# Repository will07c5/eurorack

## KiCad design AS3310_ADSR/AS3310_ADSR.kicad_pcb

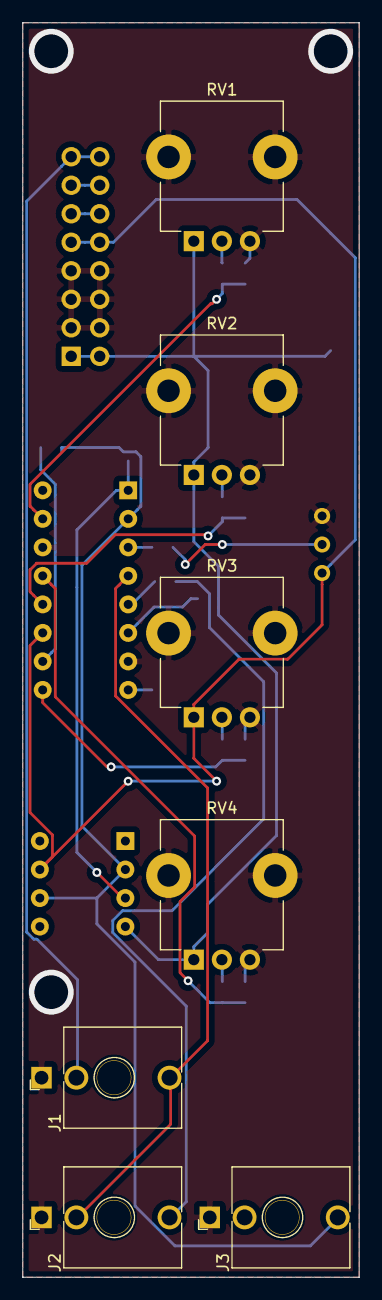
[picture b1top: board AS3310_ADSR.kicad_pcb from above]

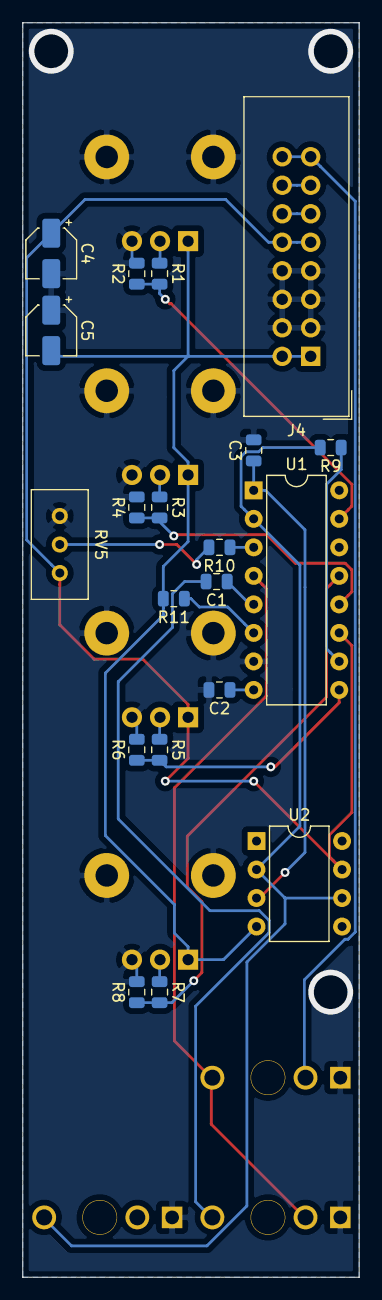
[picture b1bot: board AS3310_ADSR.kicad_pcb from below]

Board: 2 copper layers, 30.0 x 111.8 mm, 27 parts (20 on the bottom side), 24 nets.

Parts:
C1: 3nF; C_0805_2012Metric
C2: 10nF; C_0805_2012Metric
C3: 39nF; C_0805_2012Metric
C4, C5: CP1; CP_Elec_4x3
J1: Gate; Jack_3.5mm_QingPu_WQP-PJ398SM_Vertical_CircularHoles
J2: Trigger; Jack_3.5mm_QingPu_WQP-PJ398SM_Vertical_CircularHoles
J3: Env; Jack_3.5mm_QingPu_WQP-PJ398SM_Vertical_CircularHoles
J4: Conn_01x16; IDC-Header_2x08_P2.54mm_Vertical
R1, R3, R7: 22K; R_0805_2012Metric
R2, R4, R8: 450; R_0805_2012Metric
R5, R6: R_US; R_0805_2012Metric
R9: 30K; R_0805_2012Metric
R10: 10K; R_0805_2012Metric
R11: 470; R_0805_2012Metric
RV1, RV2, RV3: 100K; Potentiometer_TT_P0915N
RV4: R_POT_US; Potentiometer_TT_P0915N
RV5: 100K; Potentiometer_Bourns_3296W_Vertical
U1: AS3310; DIP-16_W7.62mm
U2: TL071; DIP-8_W7.62mm

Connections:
+5V: J4.11, J4.12
+12V: C4.1, J4.9, J4.10, RV3.1, RV5.1, U1.11, U2.7
-12V: C5.2, J4.1, J4.2, R11.2, RV1.1, RV2.1, RV4.1, U2.4
/Attack: R1.2, R2.1, U1.15
/Decay: R3.2, R4.1, U1.12
/Gate: J1.T, J2.TN, U1.4
/Rear_CV: J4.13, J4.14
/Rear_Gate: J1.TN, J4.15, J4.16
/Release: R7.2, R8.1, U1.13
/Sustain: R5.2, R6.1, U1.9
/Trigger: C1.2, J2.T
GNDREF: C2.2, C3.2, C4.2, C5.1, J1.S, J2.S, J3.S, J4.3, J4.4, J4.5, J4.6, J4.7, J4.8, R2.2, R4.2, R6.2, R8.2, RV1.3, RV2.3, RV3.3, RV4.3, RV5.3, U1.7, U1.14
unnamed: C1.1, U1.5
unnamed: C2.1, U1.8
unnamed: C3.1, U1.1, U2.3
unnamed: J3.T, R9.2, U1.2, U2.2, U2.6
unnamed: R1.1, RV1.2
unnamed: R3.1, RV2.2
unnamed: R5.1, RV3.2
unnamed: R7.1, RV4.2
unnamed: R9.1, U1.10
unnamed: R10.1, U1.3
unnamed: R10.2, RV5.2
unnamed: R11.1, U1.6

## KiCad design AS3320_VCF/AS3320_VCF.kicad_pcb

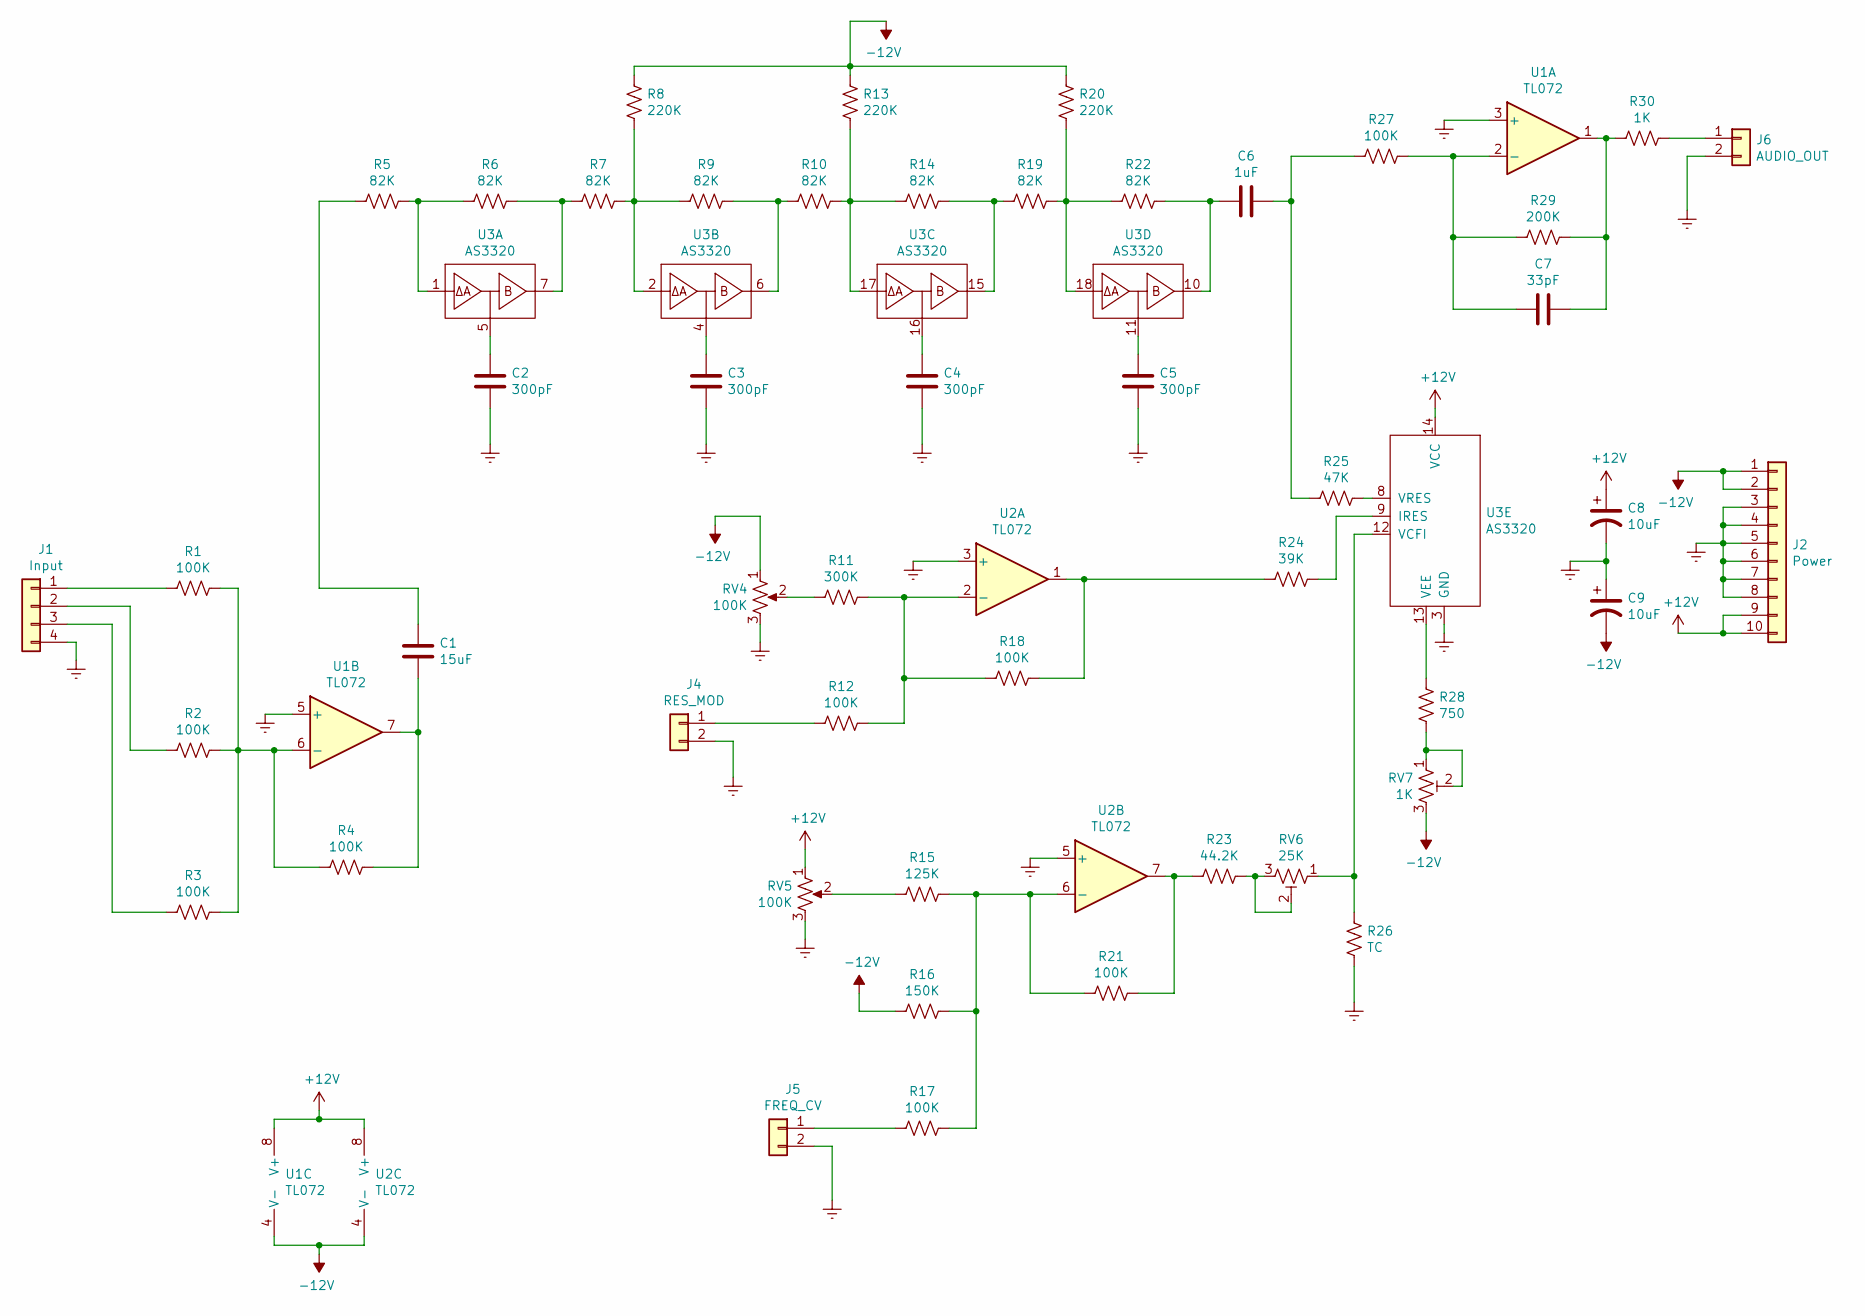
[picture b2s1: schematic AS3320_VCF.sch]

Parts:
C1: 15uF; C_0805_2012Metric
C2, C3, C4, C5: 300pF; Mica_Cap
C6: 1uF; C_0805_2012Metric
C7: 33pF; C_0805_2012Metric
C8, C9: 10uF; CP_Elec_4x3
J1: Input; PinHeader_1x04_P2.54mm_Vertical
J2: Power; IDC-Header_2x05_P2.54mm_Vertical
J4: RES_MOD; PinHeader_1x02_P2.54mm_Vertical
J5: FREQ_CV; PinHeader_1x02_P2.54mm_Vertical
J6: AUDIO_OUT; PinHeader_1x02_P2.54mm_Vertical
R1, R2, R3, R4, R12, R17, R18, R21, R27: 100K; R_0805_2012Metric
R5, R6, R7, R9, R10, R14, R19, R22: 82K; R_0805_2012Metric
R8, R13, R20: 220K; R_0805_2012Metric
R11: 300K; R_0805_2012Metric
R15: 125K; R_0805_2012Metric
R16: 150K; R_0805_2012Metric
R23: 44.2K; R_0805_2012Metric
R24: 39K; R_0805_2012Metric
R25: 47K; R_0805_2012Metric
R26: TC; Tempco
R28: 750; R_0805_2012Metric
R29: 200K; R_0805_2012Metric
R30: 1K; R_0805_2012Metric
RV4, RV5: 100K; PinHeader_1x03_P2.54mm_Vertical
RV6: 25K; Potentiometer_Bourns_3296W_Vertical
RV7: 1K; Potentiometer_Bourns_3296W_Vertical
U1, U2: TL072; DIP-8_W7.62mm
U3: AS3320; DIP-18_W7.62mm

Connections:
+12V: C8.1, J2.9, J2.10, RV5.1, U1.8 (V+), U2.8 (V+), U3.14 (VCC)
-12V: C9.2, J2.1, J2.2, R8.1, R13.1, R16.2, R20.1, RV4.1, RV7.3, U1.4 (V-), U2.4 (V-)
GNDREF: C2.2, C3.2, C4.2, C5.2, C8.2, C9.1, J1.4, J2.3, J2.4, J2.5, J2.6, J2.7, J2.8, J4.2, J5.2, J6.2, R26.2, RV4.3, RV5.3, U1.3 (+), U1.5 (+), U2.3 (+), U2.5 (+), U3.3 (GND)
unnamed: C1.1, R5.2
unnamed: C1.2, R4.1, U1.7
unnamed: C2.1, U3.5
unnamed: C3.1, U3.4
unnamed: C4.1, U3.16
unnamed: C5.1, U3.11
unnamed: C6.1, R25.2, R27.2
unnamed: C6.2, R22.1, U3.10
unnamed: C7.1, R27.1, R29.2, U1.2 (-)
unnamed: C7.2, R29.1, R30.2, U1.1
unnamed: J1.1, R1.2
unnamed: J1.2, R2.2
unnamed: J1.3, R3.2
unnamed: J4.1, R12.2
unnamed: J5.1, R17.2
unnamed: J6.1, R30.1
unnamed: R1.1, R2.1, R3.1, R4.2, U1.6 (-)
unnamed: R5.1, R6.2, U3.1
unnamed: R6.1, R7.2, U3.7
unnamed: R7.1, R8.2, R9.2, U3.2
unnamed: R10.1, R13.2, R14.2, U3.17
unnamed: R9.1, R10.2, U3.6
unnamed: R11.1, R12.1, R18.2, U2.2 (-)
unnamed: R11.2, RV4.2
unnamed: R14.1, R19.2, U3.15
unnamed: R15.1, R16.1, R17.1, R21.2, U2.6 (-)
unnamed: R15.2, RV5.2
unnamed: R18.1, R24.2, U2.1
unnamed: R19.1, R20.2, R22.2, U3.18
unnamed: R21.1, R23.2, U2.7
unnamed: R23.1, RV6.2, RV6.3
unnamed: R24.1, U3.9 (IRES)
unnamed: R25.1, U3.8 (VRES)
unnamed: R26.1, RV6.1, U3.12 (VCFI)
unnamed: R28.1, U3.13 (VEE)
unnamed: R28.2, RV7.1, RV7.2

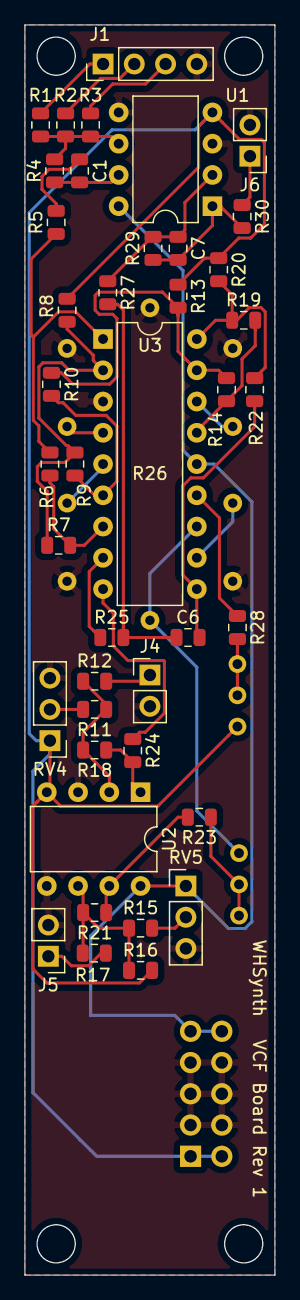
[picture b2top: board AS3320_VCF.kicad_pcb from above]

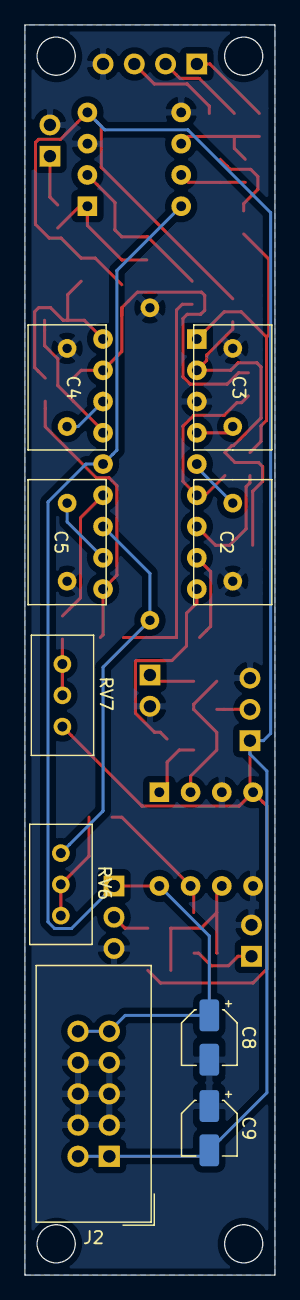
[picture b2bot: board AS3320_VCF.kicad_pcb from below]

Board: 2 copper layers, 20.3 x 101.6 mm, 51 parts (9 on the bottom side), 39 nets.

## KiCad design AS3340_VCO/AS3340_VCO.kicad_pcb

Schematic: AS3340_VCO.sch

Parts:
C1: 1nF; Mica_cap
C2: 100nF; C_0805_2012Metric
C3, C4: 10nF; C_0805_2012Metric
C5, C6: 1nF; C_0805_2012Metric
C7: 560pF; C_0805_2012Metric
C8, C9: 10uF; CP_Elec_4x3
J1: Conn_01x14; PinHeader_1x14_P2.54mm_Vertical
J3: Power; IDC-Header_2x08_P2.54mm_Vertical
JP5: Jumper; PinHeader_1x02_P2.54mm_Vertical
R1: 100K; R_0805_2012Metric
R2, R11: 470; R_0805_2012Metric
R3: 22K; R_0805_2012Metric
R4: 18K; R_0805_2012Metric
R5, R13: 5.6K; R_0805_2012Metric
R6: 1K; R_0805_2012Metric
R7: 680; R_0805_2012Metric
R8: 51K; R_0805_2012Metric
R9: 1M; R_0805_2012Metric
R10: 1.2M; R_0805_2012Metric
RV1: 5K; Potentiometer_Bourns_3296W_Vertical
RV2: 10K; Potentiometer_Bourns_3296W_Vertical
RV3: 1K; Potentiometer_Bourns_3296W_Vertical
RV4: 100K; Potentiometer_Bourns_3296W_Vertical
TP1, TP2: TestPoint; TestPoint_Pad_D2.0mm
U1: AS3340; DIP-16_W7.62mm

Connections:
+5V: J3.11, J3.12
+12V: C8.1, J1.2, J3.9, J3.10, RV2.1, RV4.1, U1.16 (VCC); also elsewhere on the board
-12V: C9.2, J1.3, J3.1, J3.2, R7.2; also elsewhere on the board
/CV: J1.5, R1.1, R2.2, U1.15 (VFCI)
/LIN: C2.2, J1.6
/Output Conditioning/RAW_PULSE: R8.2, U1.4 (VP); also elsewhere on the board
/Output Conditioning/RAW_RAMP: U1.8 (VSO); also elsewhere on the board
/Output Conditioning/RAW_TRI: U1.10 (VTO); also elsewhere on the board
/PWM: J1.4, U1.5 (VPWM)
/Pulse: J1.9; also elsewhere on the board
/REAR_CV: J1.8, J3.13, J3.14
/REAR_GATE: J3.15, J3.16
/Ramp: J1.10; also elsewhere on the board
/SYNC: C5.2, J1.7
/Saw: J1.11; also elsewhere on the board
/Sine: J1.13; also elsewhere on the board
/Tri: J1.12; also elsewhere on the board
/Vee: R5.1, R7.1, R13.1, U1.3 (VEE)
GNDREF: C1.1, C3.1, C4.1, C6.2, C7.1, C8.2, C9.1, J1.1, J1.14, J3.3, J3.4, J3.5, J3.6, J3.7, J3.8, JP5.2, R3.1, R8.1, RV3.2, RV3.3, U1.12 (GND); also elsewhere on the board
unnamed: C1.2, U1.11 (CAP)
unnamed: C2.1, R9.2
unnamed: C3.2, R2.1
unnamed: C4.2, R11.1
unnamed: C5.1, U1.6 (VHSI)
unnamed: C6.1, U1.9 (VSSI)
unnamed: C7.2, JP5.1, R6.2, U1.14 (VS)
unnamed: R1.2, RV4.2, RV4.3
unnamed: R3.2, RV2.3
unnamed: R4.1, RV1.1
unnamed: R4.2, U1.1 (SCALE1)
unnamed: R5.2, TP1.1, U1.2 (SCALE2)
unnamed: R6.1, RV3.1
unnamed: R9.1, R10.1, R11.2, U1.13 (VLFI)
unnamed: R10.2, RV2.2
unnamed: R13.2, RV1.2, RV1.3, TP2.1

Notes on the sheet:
Scale Trim

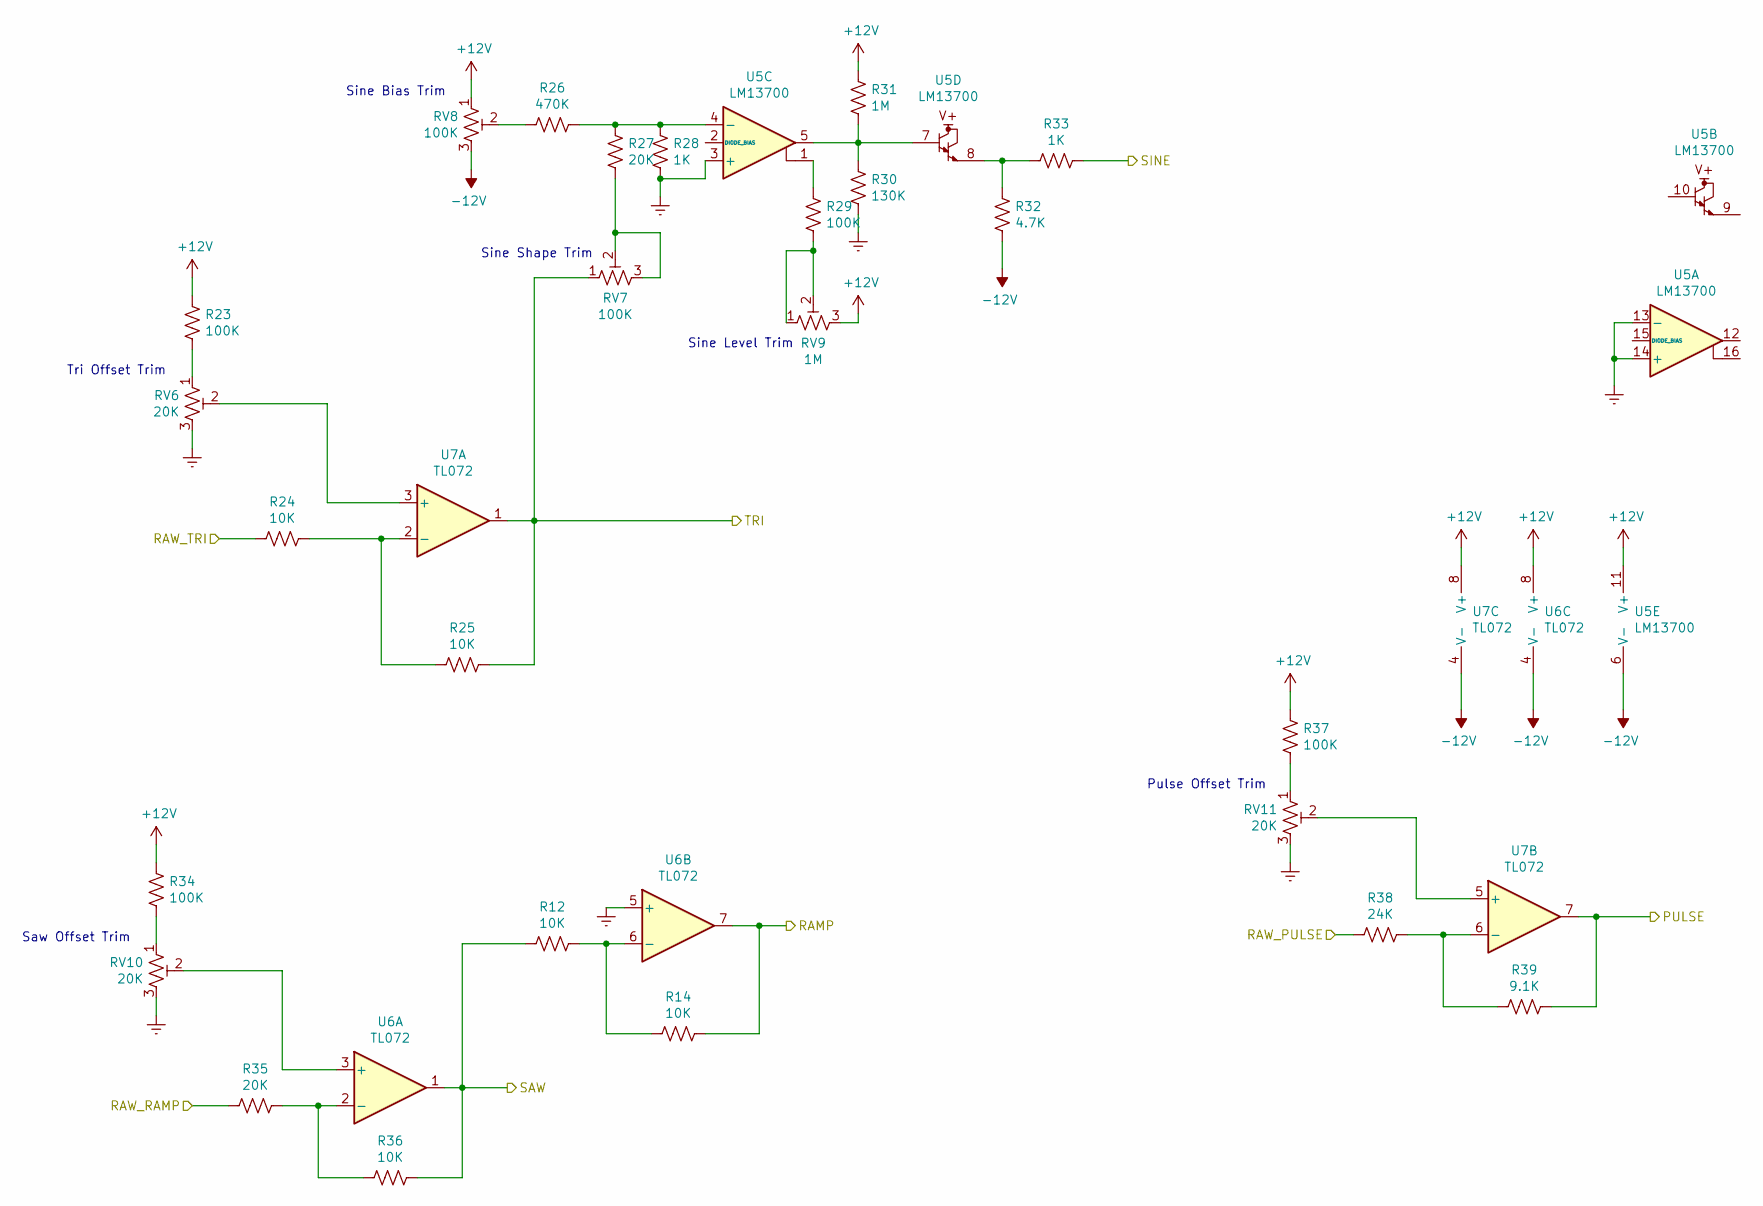
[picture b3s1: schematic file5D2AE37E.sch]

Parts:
R12, R14, R24, R25, R36: 10K; R_0805_2012Metric
R23, R29, R34, R37: 100K; R_0805_2012Metric
R26: 470K; R_0805_2012Metric
R27, R35: 20K; R_0805_2012Metric
R28, R33: 1K; R_0805_2012Metric
R30: 130K; R_0805_2012Metric
R31: 1M; R_0805_2012Metric
R32: 4.7K; R_0805_2012Metric
R38: 24K; R_0805_2012Metric
R39: 9.1K; R_0805_2012Metric
RV6, RV10, RV11: 20K; Potentiometer_Bourns_3296W_Vertical
RV7, RV8: 100K; Potentiometer_Bourns_3296W_Vertical
RV9: 1M; Potentiometer_Bourns_3296W_Vertical
U5: LM13700; DIP-16_W7.62mm
U6, U7: TL072; DIP-8_W7.62mm

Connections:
+12V: R23.1, R31.1, R34.1, R37.1, RV8.1, RV9.3, U5.11 (V+), U6.8 (V+), U7.8 (V+); also elsewhere on the board
-12V: R32.2, RV8.3, U5.6 (V-), U6.4 (V-), U7.4 (V-); also elsewhere on the board
/Output Conditioning/RAW_PULSE: R38.1; also elsewhere on the board
/Output Conditioning/RAW_RAMP: R35.1; also elsewhere on the board
/Output Conditioning/RAW_TRI: R24.1; also elsewhere on the board
/Pulse: R39.2, U7.7; also elsewhere on the board
/Ramp: R14.2, U6.7; also elsewhere on the board
/Saw: R12.1, R36.2, U6.1; also elsewhere on the board
/Sine: R33.2; also elsewhere on the board
/Tri: R25.2, RV7.1, U7.1; also elsewhere on the board
GNDREF: R28.2, R30.2, RV6.3, RV10.3, RV11.3, U5.3 (+), U5.13 (-), U5.14 (+), U6.5 (+); also elsewhere on the board
unnamed: R12.2, R14.1, U6.6 (-)
unnamed: R23.2, RV6.1
unnamed: R24.2, R25.1, U7.2 (-)
unnamed: R26.1, RV8.2
unnamed: R26.2, R27.1, R28.1, U5.4 (-)
unnamed: R27.2, RV7.2, RV7.3
unnamed: R29.1, U5.1
unnamed: R29.2, RV9.1, RV9.2
unnamed: R30.1, R31.2, U5.5, U5.7
unnamed: R32.1, R33.1, U5.8
unnamed: R34.2, RV10.1
unnamed: R35.2, R36.1, U6.2 (-)
unnamed: R37.2, RV11.1
unnamed: R38.2, R39.1, U7.6 (-)
unnamed: RV6.2, U7.3 (+)
unnamed: RV10.2, U6.3 (+)
unnamed: RV11.2, U7.5 (+)

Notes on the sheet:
Tri Offset Trim
Sine Bias Trim
Sine Shape Trim
Sine Level Trim
Saw Offset Trim
Pulse Offset Trim

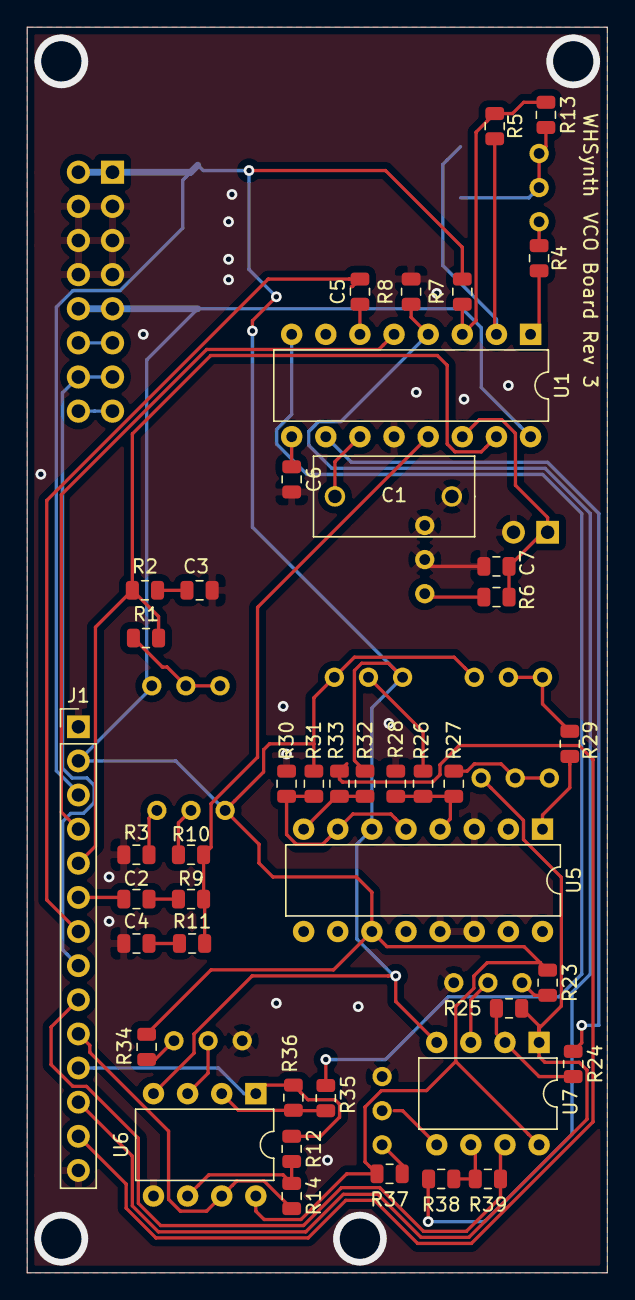
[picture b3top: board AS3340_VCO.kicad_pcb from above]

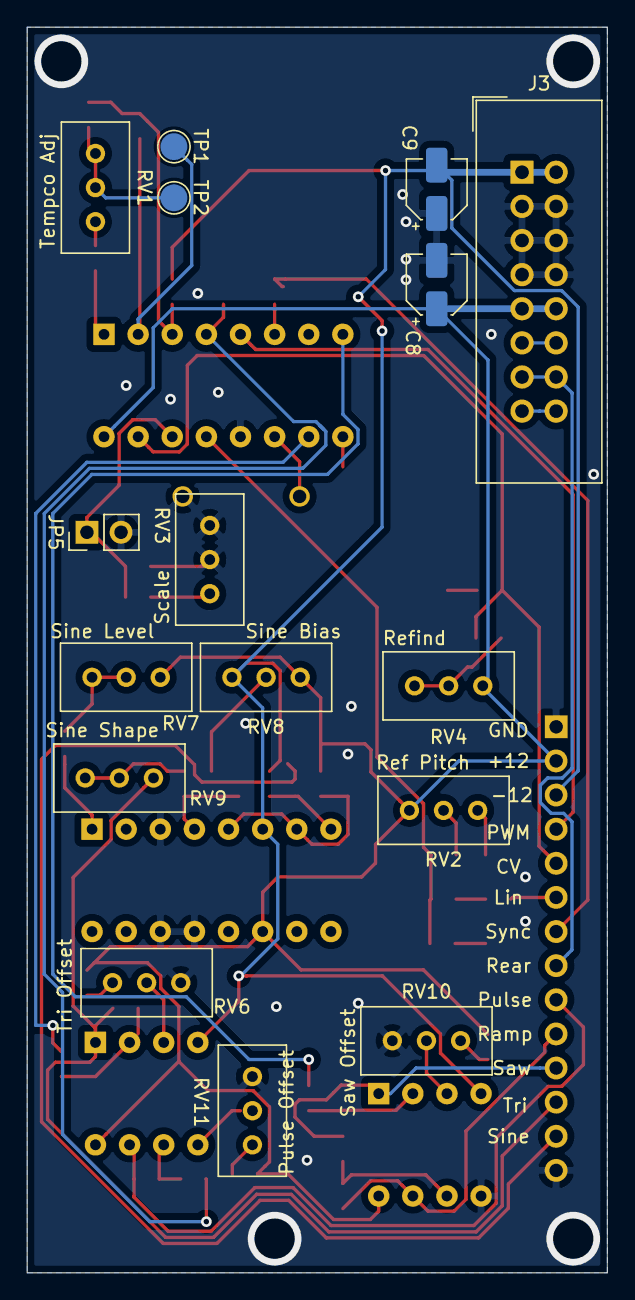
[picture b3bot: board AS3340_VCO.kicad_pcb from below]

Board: 2 copper layers, 43.2 x 92.7 mm, 59 parts (16 on the bottom side), 52 nets.

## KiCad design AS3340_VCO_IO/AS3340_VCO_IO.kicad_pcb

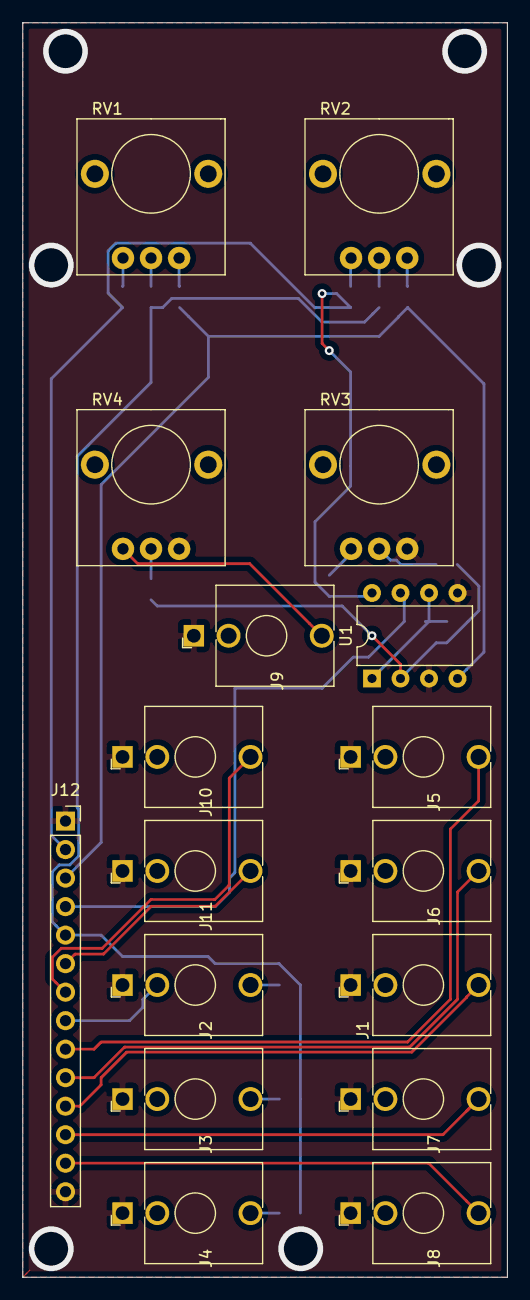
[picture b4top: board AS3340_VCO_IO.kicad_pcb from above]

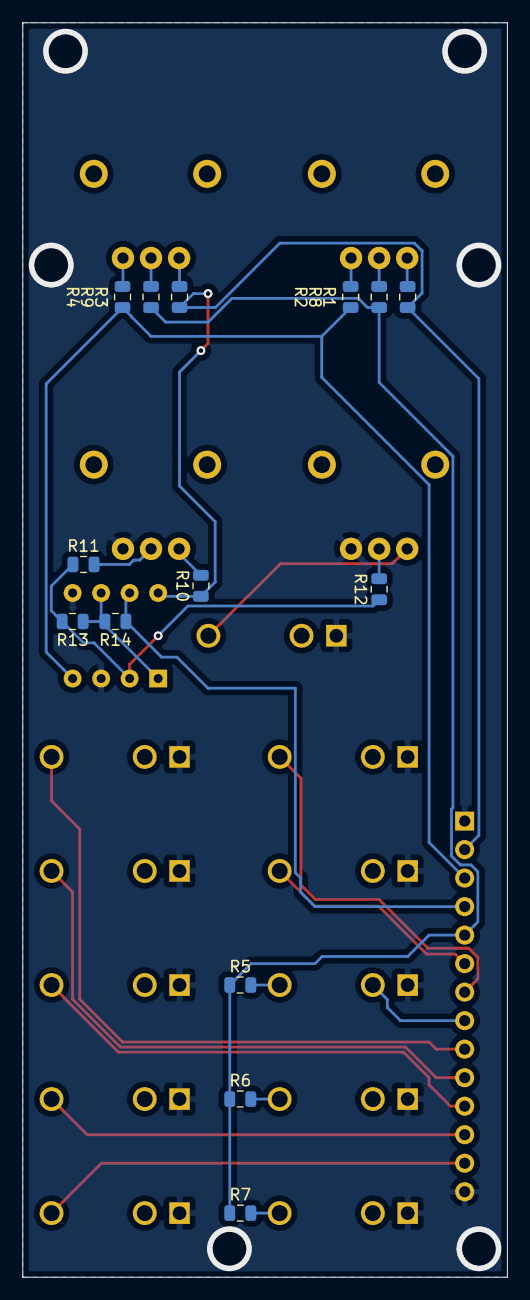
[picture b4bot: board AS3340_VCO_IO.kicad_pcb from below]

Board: 2 copper layers, 43.2 x 111.8 mm, 31 parts (14 on the bottom side), 28 nets.

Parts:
J1: Saw; Jack_3.5mm_QingPu_WQP-PJ398SM_Vertical_CircularHoles
J2: CV1; Jack_3.5mm_QingPu_WQP-PJ398SM_Vertical_CircularHoles
J3: CV2; Jack_3.5mm_QingPu_WQP-PJ398SM_Vertical_CircularHoles
J4: CV3; Jack_3.5mm_QingPu_WQP-PJ398SM_Vertical_CircularHoles
J5: Pulse; Jack_3.5mm_QingPu_WQP-PJ398SM_Vertical_CircularHoles
J6: Ramp; Jack_3.5mm_QingPu_WQP-PJ398SM_Vertical_CircularHoles
J7: Tri; Jack_3.5mm_QingPu_WQP-PJ398SM_Vertical_CircularHoles
J8: Sine; Jack_3.5mm_QingPu_WQP-PJ398SM_Vertical_CircularHoles
J9: PWM; Jack_3.5mm_QingPu_WQP-PJ398SM_Vertical_CircularHoles
J10: Sync; Jack_3.5mm_QingPu_WQP-PJ398SM_Vertical_CircularHoles
J11: LIN; Jack_3.5mm_QingPu_WQP-PJ398SM_Vertical_CircularHoles
J12: IO; PinSocket_1x14_P2.54mm_Vertical
R1, R2, R3, R4, R10: 200K; R_0805_2012Metric
R5, R6, R7, R8, R11, R12, R13, R14: 100K; R_0805_2012Metric
R9: 1M; R_0805_2012Metric
RV1, RV2, RV3, RV4: 100K; TT_P0915N
U1: TL072; DIP-8_W7.62mm

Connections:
+12V: J12.2, R1.1, R3.1, R10.1, U1.8
-12V: J12.3, R2.2, R4.2, U1.4
/CV: J12.5, R5.1, R6.1, R7.1, R8.1, R9.1
/LIN: J11.T, J12.6
/PWM: J12.4, R14.1, U1.7
/Pulse: J5.T, J12.9
/REAR_CV: J2.TN, J12.8
/Ramp: J6.T, J12.10
/SYNC: J10.T, J12.7
/Saw: J1.T, J12.11
/Sine: J8.T, J12.13
/Tri: J7.T, J12.12
GNDREF: J1.S, J2.S, J3.S, J4.S, J5.S, J6.S, J7.S, J8.S, J9.S, J10.S, J11.S, J12.1, J12.14, RV3.3, RV4.3, U1.3, U1.5
unnamed: J2.T, R5.2
unnamed: J3.T, R6.2
unnamed: J4.T, R7.2
unnamed: J9.T, RV4.1
unnamed: R1.2, RV1.1
unnamed: R2.1, RV1.3
unnamed: R3.2, RV2.1
unnamed: R4.1, RV2.3
unnamed: R8.2, RV1.2
unnamed: R9.2, RV2.2
unnamed: R10.2, RV3.1
unnamed: R11.1, R12.1, R13.2, U1.2
unnamed: R11.2, RV3.2
unnamed: R12.2, RV4.2
unnamed: R13.1, R14.2, U1.1, U1.6

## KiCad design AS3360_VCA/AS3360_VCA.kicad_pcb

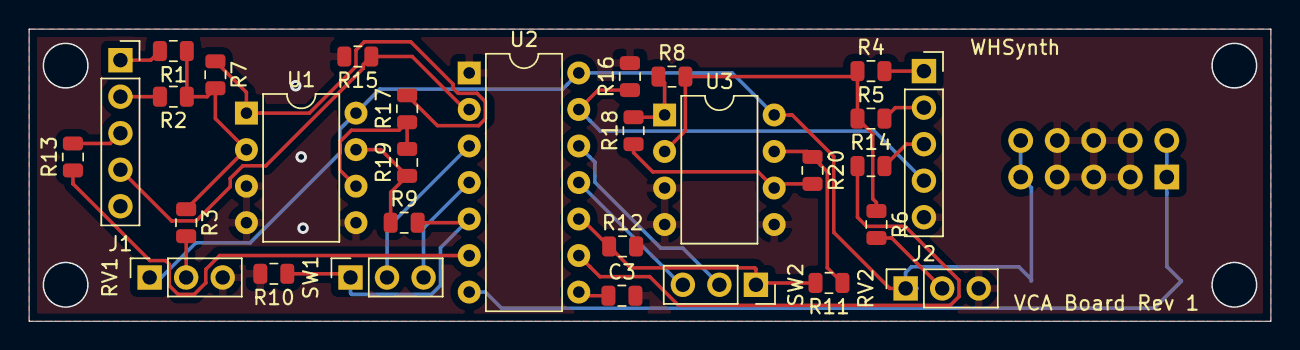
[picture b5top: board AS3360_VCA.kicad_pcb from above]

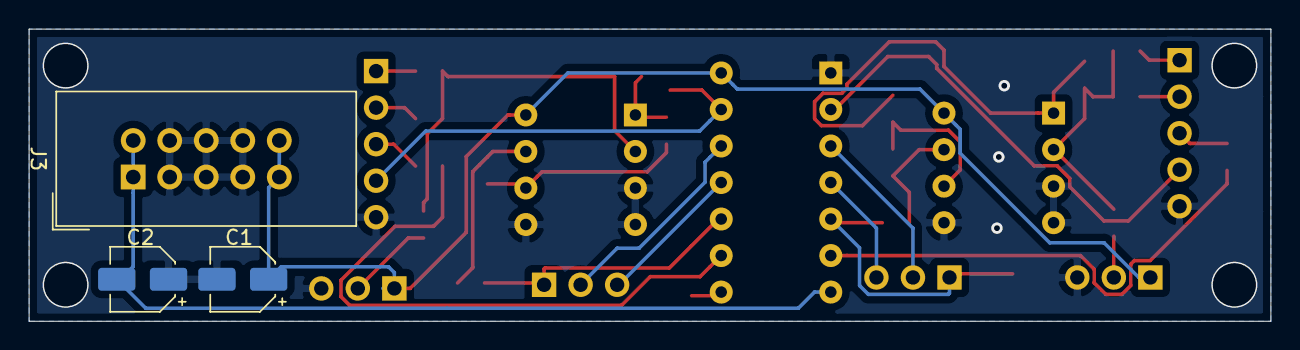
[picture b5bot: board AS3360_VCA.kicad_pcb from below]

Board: 2 copper layers, 86.4 x 20.3 mm, 33 parts (3 on the bottom side), 30 nets.

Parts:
C1, C2: 10uF; CP_Elec_4x3
C3: 5nF; C_0805_2012Metric
J1: VCA_IO_A; PinSocket_1x05_P2.54mm_Vertical
J2: VCA_IO_B; PinSocket_1x05_P2.54mm_Vertical
J3: Power; IDC-Header_2x05_P2.54mm_Vertical
R1, R2, R3, R4, R5, R6, R7, R8, R9, R11, R17, R18, R19, R20: 100K; R_0805_2012Metric
R10, R12: 20K; R_0805_2012Metric
R13, R14, R15, R16: 47K; R_0805_2012Metric
RV1, RV2: 100K; PinSocket_1x03_P2.54mm_Vertical
SW1, SW2: LIN_LOG; PinSocket_1x03_P2.54mm_Vertical
U1, U3: TL072; DIP-8_W7.62mm
U2: AS3360; DIP-14_W7.62mm

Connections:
+12V: C1.1, J3.9, J3.10, RV1.1, RV2.1, U1.8, U2.14, U3.8
-12V: C2.2, J3.1, J3.2, U2.7
GNDREF: C1.2, C2.1, C3.2, J1.5, J2.5, J3.3, J3.4, J3.5, J3.6, J3.7, J3.8, R10.2, R12.2, R15.2, R16.2, RV1.3, RV2.3, U1.3, U1.4, U1.5, U2.1, U3.3, U3.4, U3.5
unnamed: C3.1, U2.8
unnamed: J1.1, R1.2
unnamed: J1.2, R2.2
unnamed: J1.3, R13.2
unnamed: J1.4, R15.1, U2.2
unnamed: J2.1, R4.2
unnamed: J2.2, R5.2
unnamed: J2.3, R14.2
unnamed: J2.4, R16.1, U2.13
unnamed: R1.1, R2.1, R3.1, R7.2, U1.2
unnamed: R3.2, RV1.2
unnamed: R4.1, R5.1, R6.1, R8.2, U3.2
unnamed: R6.2, RV2.2
unnamed: R9.2, R10.1, SW1.1, U2.5
unnamed: R11.1, R20.1, U3.7
unnamed: R11.2, R12.1, SW2.1, U2.10
unnamed: R13.1, U2.6
unnamed: R14.1, U2.9
unnamed: R17.1, R19.2, U1.6
unnamed: R7.1, R17.2, U1.1
unnamed: R18.1, R20.2, U3.6
unnamed: R8.1, R18.2, U3.1
unnamed: R9.1, R19.1, U1.7
unnamed: SW1.2, U2.3
unnamed: SW1.3, U2.4
unnamed: SW2.2, U2.12
unnamed: SW2.3, U2.11
